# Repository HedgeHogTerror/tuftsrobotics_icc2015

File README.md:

# tuftsrobotics_icc2015
Code repository for Tufts Robotics Club Intel-Cornell Cup Project 2015

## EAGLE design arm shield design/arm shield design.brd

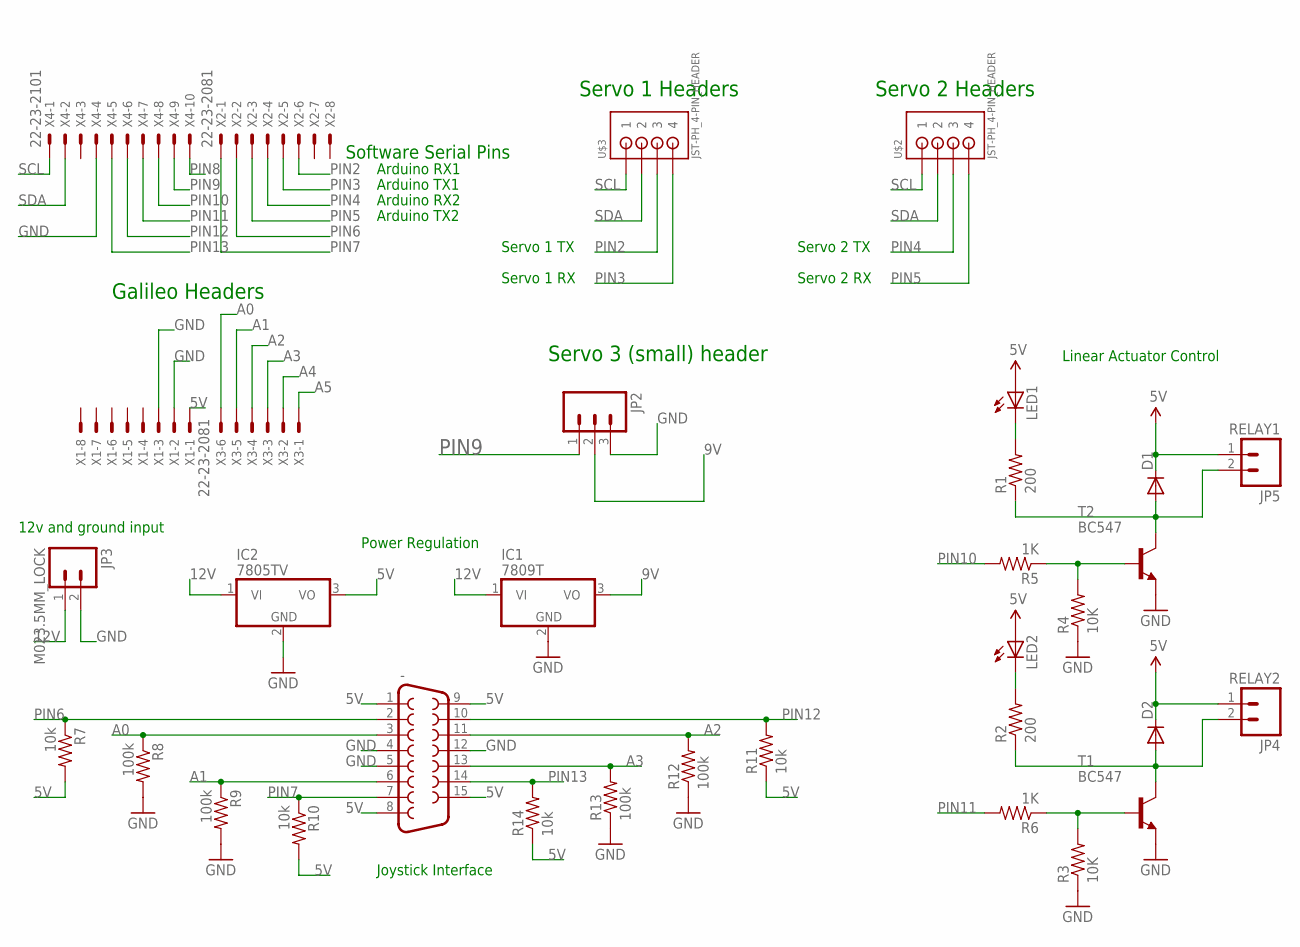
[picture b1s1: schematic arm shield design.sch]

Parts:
-: F15HP
D1, D2: DIODE1N4148; DIODE-1N4148
IC1: 7809T; TO220V
IC2: 7805TV; TO220V
JP2: M03PTH; 1X03
JP3: M023.5MM_LOCK; SCREWTERMINAL-3.5MM-2_LOCK
JP4: RELAY2; SCREWTERMINAL-3.5MM-2_LOCK
JP5: RELAY1; SCREWTERMINAL-3.5MM-2_LOCK
LED1, LED2: LED3MM
R1, R2: 200; AXIAL-0.1
R3, R4: 10K; AXIAL-0.1
R5, R6: 1K; AXIAL-0.1
R7, R10, R11, R14: 10k; AXIAL-0.1
R8, R9, R12, R13: 100k; AXIAL-0.1
T1, T2: BC547; TO92
U$2, U$3: JST-PH_4-PIN_HEADER; JST_B4B-PH_HEADER; MPN S4B-PH-K-S(LF)(SN)
X1, X2: 22-23-2081
X3: 22-23-2061
X4: 22-23-2101

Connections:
5V: -.1, -.8, -.9, -.15, D1.C, D2.C, IC2.3 (VO), JP4.1, JP5.1, LED1.A, LED2.A, R7.P$2 (2), R10.P$2 (2), R11.P$1 (1), R14.P$1 (1), X1.1
9V: IC1.3 (VO), JP2.2
12V: IC1.1 (VI), IC2.1 (VI), JP3.1
A0: -.3, R8.P$1 (1), X3.6
A1: -.6, R9.P$1 (1), X3.5
A2: -.11, R12.P$2 (2), X3.4
A3: -.13, R13.P$2 (2), X3.3
A4: X3.2
A5: X3.1
GND: -.4, -.5, -.12, IC1.2 (GND), IC2.2 (GND), JP2.3, JP3.2, R3.P$1 (1), R4.P$1 (1), R8.P$2 (2), R9.P$2 (2), R12.P$1 (1), R13.P$1 (1), T1.1 (E), T2.1 (E), X1.2, X1.3, X4.4
unnamed: D1.A, JP5.2, R1.P$1 (1), T2.3 (C)
unnamed: D2.A, JP4.2, R2.P$1 (1), T1.3 (C)
unnamed: LED1.K (C), R1.P$2 (2)
unnamed: R3.P$2 (2), R6.P$1 (1), T1.2 (B)
unnamed: LED2.K (C), R2.P$2 (2)
unnamed: R4.P$2 (2), R5.P$1 (1), T2.2 (B)
PIN2: U$3.P3 (3), X2.6
PIN3: U$3.P4 (4), X2.5
PIN4: U$2.P3 (3), X2.4
PIN5: U$2.P4 (4), X2.3
PIN6: -.2, R7.P$1 (1), X2.2
PIN7: -.7, R10.P$1 (1), X2.1
PIN8: X4.10
PIN9: JP2.1, X4.9
PIN10: R5.P$2 (2), X4.8
PIN11: R6.P$2 (2), X4.7
PIN12: -.10, R11.P$2 (2), X4.6
PIN13: -.14, R14.P$2 (2), X4.5
SCL: U$2.P1 (1), U$3.P1 (1), X4.1
SDA: U$2.P2 (2), U$3.P2 (2), X4.2

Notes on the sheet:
Arduino RX1
Arduino TX1
Arduino RX2
Arduino TX2
Galileo Headers
Servo 1 Headers
Servo 1 TX
Servo 1 RX
Software Serial Pins
Servo 2 Headers
Servo 2 TX
Servo 2 RX
Servo 3 (small) header
12v and ground input
Linear Actuator Control
Power Regulation
Joystick Interface

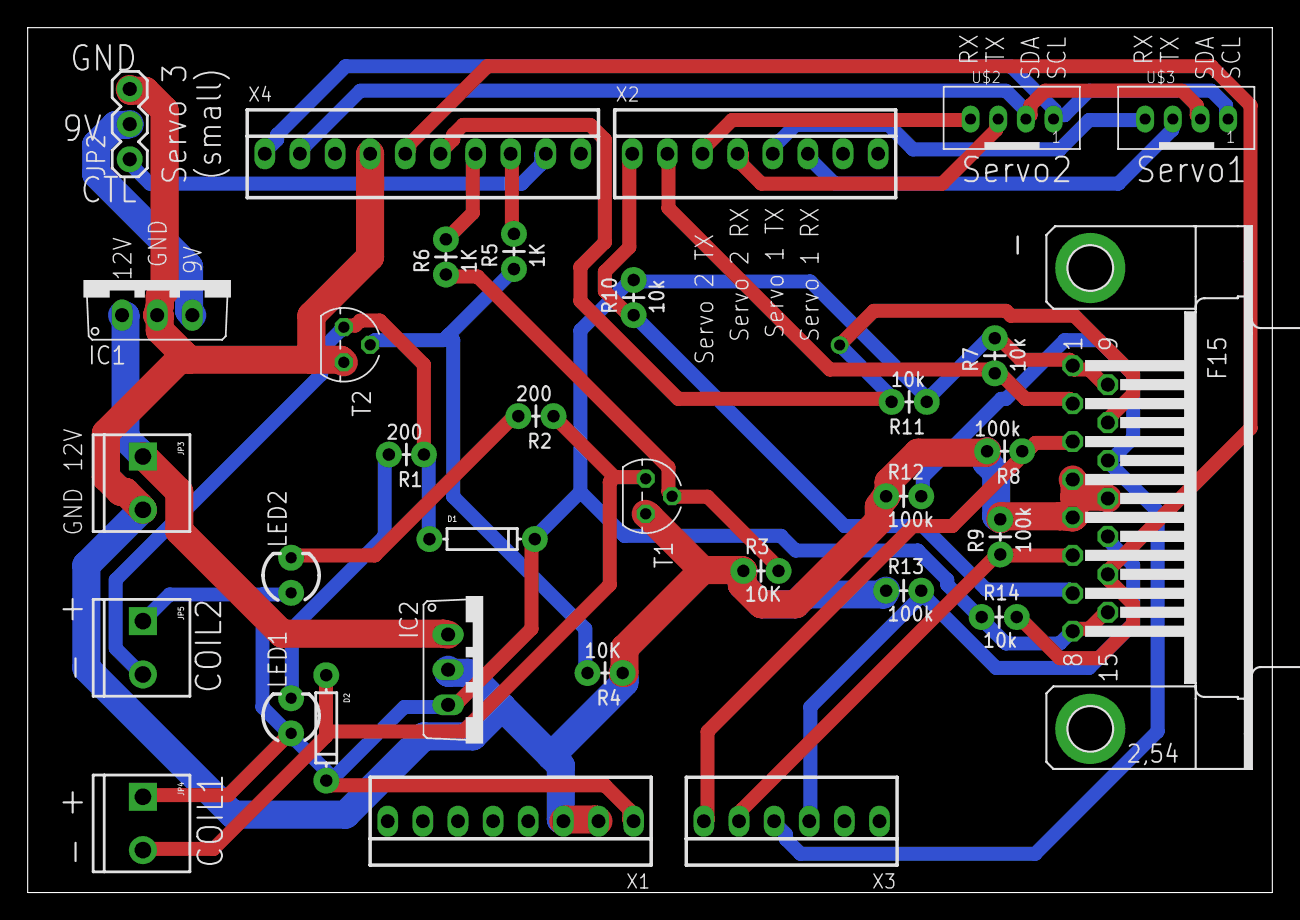
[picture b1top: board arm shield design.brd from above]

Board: 2 copper layers, 90.0 x 62.5 mm, 33 parts (0 on the bottom side), 27 nets.

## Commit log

2015-04-14 File dump. Test code for motors and Eagle schematic of shield
2015-04-14 Can now read position. Wrote allowing position control with the joystick
2015-04-14 Made a sketch for the main program. Also made a library for the RMCS2203 servo enabling communication of I2C
2015-04-14 Modified lib, fixed bugs
2015-04-14 Made a calibrate function which sets all servo gains to what I have observed to be nominal
2015-04-14 Renamed calibrate to defaultGains
2015-04-14 Final changes from night of 4/13
2015-04-16 change to main_sketch.ino to incorporate small servo/ roller wheel

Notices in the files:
parts and their libraries:
SparkFun-Connectors: Licensing: Creative Commons ShareAlike 4.0 International - https://creativecommons.org/licenses/by-sa/4.0
